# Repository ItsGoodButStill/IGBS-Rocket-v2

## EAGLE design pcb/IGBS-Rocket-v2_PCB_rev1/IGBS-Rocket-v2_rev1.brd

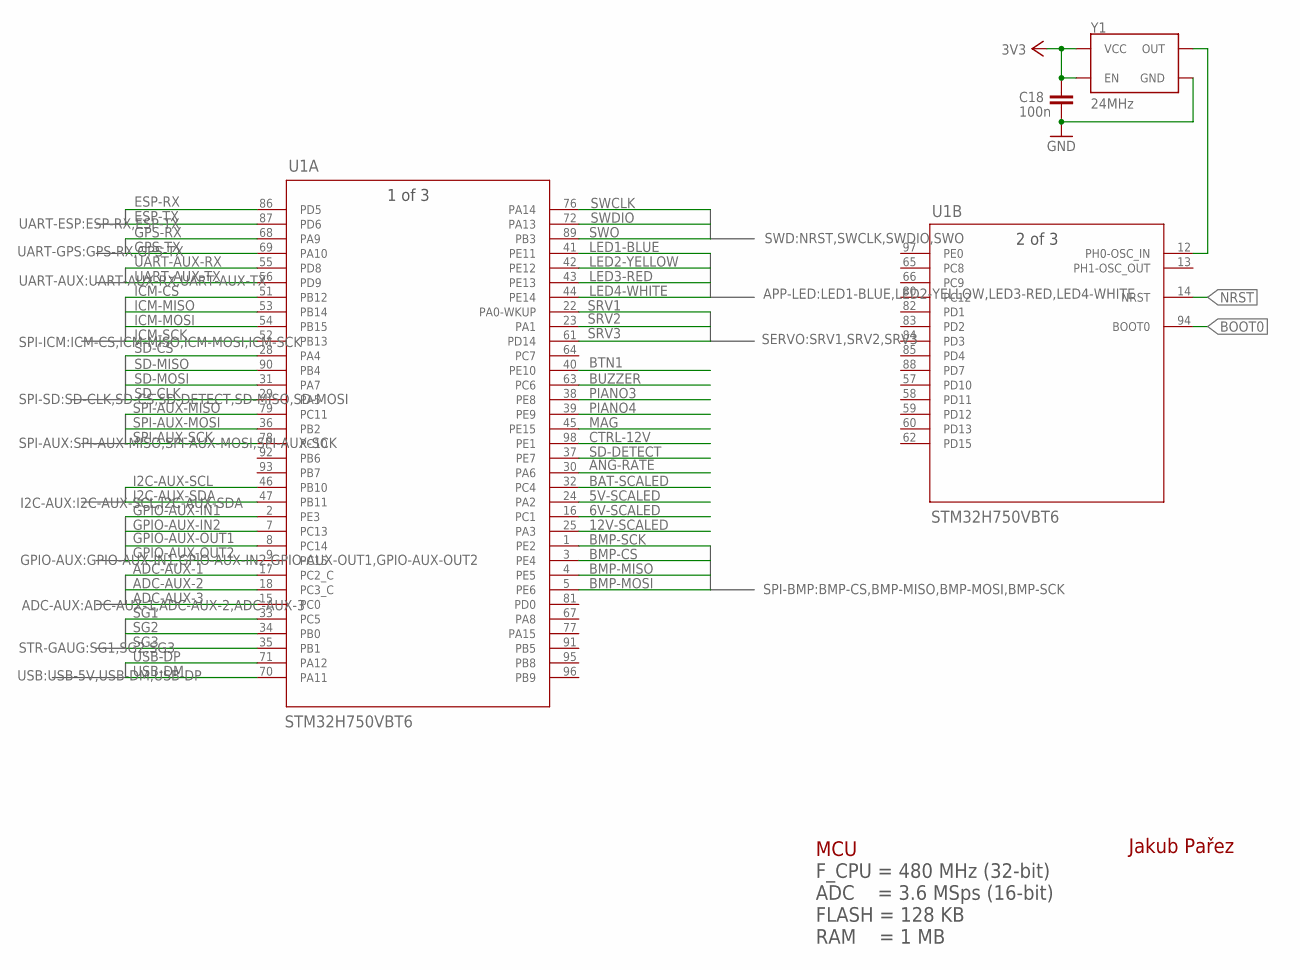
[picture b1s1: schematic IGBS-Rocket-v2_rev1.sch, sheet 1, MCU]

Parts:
C18: 100n; C0603K
U1: STM32H750VBT6; LQFP100-14X14MM
Y1: 24MHz; OSCILLATOR-SMD-7X5-4PAD

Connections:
3V3: C18.2, Y1.1 (EN), Y1.4 (VCC); also elsewhere on the board
5V-SCALED: U1.24 (PA2); also elsewhere on the board
6V-SCALED: U1.16 (PC1); also elsewhere on the board
12V-SCALED: U1.25 (PA3); also elsewhere on the board
ADC-AUX-1: U1.17 (PC2_C); also elsewhere on the board
ADC-AUX-2: U1.18 (PC3_C); also elsewhere on the board
ADC-AUX-3: U1.15 (PC0); also elsewhere on the board
ANG-RATE: U1.30 (PA6); also elsewhere on the board
BAT-SCALED: U1.32 (PC4); also elsewhere on the board
BMP-CS: U1.3 (PE4); also elsewhere on the board
BMP-MISO: U1.4 (PE5); also elsewhere on the board
BMP-MOSI: U1.5 (PE6); also elsewhere on the board
BMP-SCK: U1.1 (PE2); also elsewhere on the board
BOOT0: U1.94 (BOOT0); also elsewhere on the board
BTN1: U1.40 (PE10); also elsewhere on the board
BUZZER: U1.63 (PC6); also elsewhere on the board
CTRL-12V: U1.98 (PE1); also elsewhere on the board
ESP-RX: U1.86 (PD5); also elsewhere on the board
ESP-TX: U1.87 (PD6); also elsewhere on the board
GND: C18.1, Y1.2 (GND); also elsewhere on the board
GPIO-AUX-IN1: U1.2 (PE3); also elsewhere on the board
GPIO-AUX-IN2: U1.7 (PC13); also elsewhere on the board
GPIO-AUX-OUT1: U1.8 (PC14); also elsewhere on the board
GPIO-AUX-OUT2: U1.9 (PC15); also elsewhere on the board
GPS-RX: U1.68 (PA9); also elsewhere on the board
GPS-TX: U1.69 (PA10); also elsewhere on the board
I2C-AUX-SCL: U1.46 (PB10); also elsewhere on the board
I2C-AUX-SDA: U1.47 (PB11); also elsewhere on the board
ICM-CS: U1.51 (PB12); also elsewhere on the board
ICM-MISO: U1.53 (PB14); also elsewhere on the board
ICM-MOSI: U1.54 (PB15); also elsewhere on the board
ICM-SCK: U1.52 (PB13); also elsewhere on the board
LED1-BLUE: U1.41 (PE11); also elsewhere on the board
LED2-YELLOW: U1.42 (PE12); also elsewhere on the board
LED3-RED: U1.43 (PE13); also elsewhere on the board
LED4-WHITE: U1.44 (PE14); also elsewhere on the board
MAG: U1.45 (PE15); also elsewhere on the board
unnamed: U1.12 (PH0-OSC_IN), Y1.3 (OUT)
NRST: U1.14 (NRST); also elsewhere on the board
PIANO3: U1.38 (PE8); also elsewhere on the board
PIANO4: U1.39 (PE9); also elsewhere on the board
SD-CLK: U1.29 (PA5); also elsewhere on the board
SD-CS: U1.28 (PA4); also elsewhere on the board
SD-DETECT: U1.37 (PE7); also elsewhere on the board
SD-MISO: U1.90 (PB4); also elsewhere on the board
SD-MOSI: U1.31 (PA7); also elsewhere on the board
SG1: U1.33 (PC5); also elsewhere on the board
SG2: U1.34 (PB0); also elsewhere on the board
SG3: U1.35 (PB1); also elsewhere on the board
SPI-AUX-MISO: U1.79 (PC11); also elsewhere on the board
SPI-AUX-MOSI: U1.36 (PB2); also elsewhere on the board
SPI-AUX-SCK: U1.78 (PC10); also elsewhere on the board
SRV1: U1.22 (PA0-WKUP); also elsewhere on the board
SRV2: U1.23 (PA1); also elsewhere on the board
SRV3: U1.61 (PD14); also elsewhere on the board
SWCLK: U1.76 (PA14); also elsewhere on the board
SWDIO: U1.72 (PA13); also elsewhere on the board
SWO: U1.89 (PB3); also elsewhere on the board
UART-AUX-RX: U1.55 (PD8); also elsewhere on the board
UART-AUX-TX: U1.56 (PD9); also elsewhere on the board
USB-DM: U1.70 (PA11); also elsewhere on the board
USB-DP: U1.71 (PA12); also elsewhere on the board

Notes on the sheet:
MCU
Jakub Pařez
F_CPU = 480 MHz (32-bit) ADC = 3.6 MSps (16-bit) FLASH = 128 KB RAM = 1 MB

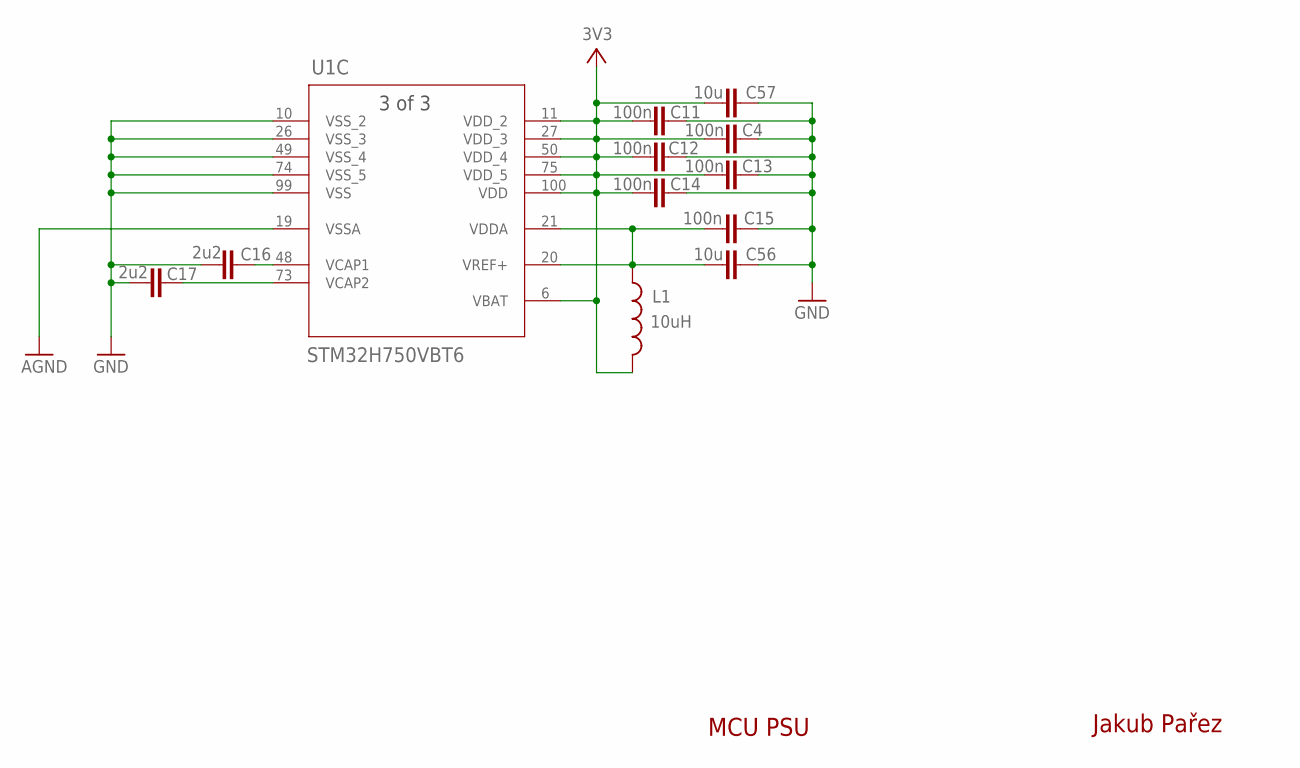
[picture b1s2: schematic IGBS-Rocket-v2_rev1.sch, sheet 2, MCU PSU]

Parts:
C4, C11, C12, C13, C14, C15: 100n; C0603K
C16, C17: 2u2; C0805K
C56, C57: 10u; 0805-CAP
L1: 10uH; 0805
U1: STM32H750VBT6; LQFP100-14X14MM

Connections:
3V3: C4.2, C11.2, C12.2, C13.2, C14.2, C57.1, L1.2, U1.6 (VBAT), U1.11 (VDD_2), U1.27 (VDD_3), U1.50 (VDD_4), U1.75 (VDD_5), U1.100 (VDD); also elsewhere on the board
AGND: U1.19 (VSSA)
GND: C4.1, C11.1, C12.1, C13.1, C14.1, C15.1, C16.2, C17.1, C56.2, C57.2, U1.10 (VSS_2), U1.26 (VSS_3), U1.49 (VSS_4), U1.74 (VSS_5), U1.99 (VSS); also elsewhere on the board
unnamed: C16.1, U1.48 (VCAP1)
unnamed: C17.2, U1.73 (VCAP2)
VDDA: C15.2, C56.1, L1.1, U1.20 (VREF+), U1.21 (VDDA)

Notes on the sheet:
MCU PSU
Jakub Pařez

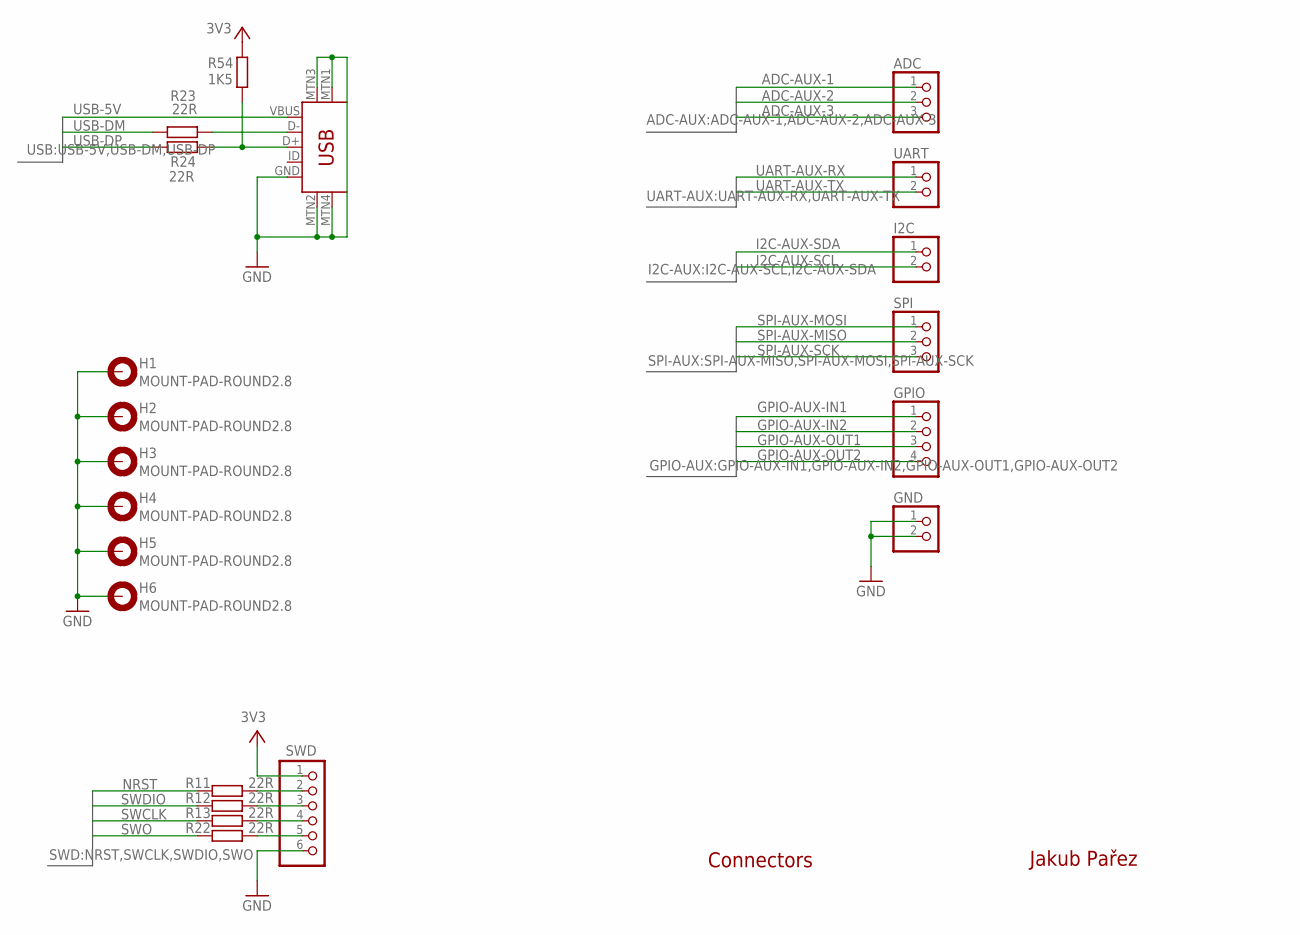
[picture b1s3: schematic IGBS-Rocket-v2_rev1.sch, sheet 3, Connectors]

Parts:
ADC: PINHD-1X3; 1X03
GND: PINHD-1X2; 1X02
GPIO: PINHD-1X4; 1X04
H1, H2, H3, H4, H5, H6: MOUNT-PAD-ROUND2.8; 2,8-PAD
I2C: PINHD-1X2; 1X02
R11, R12, R13, R22, R23, R24: 22R; R0603
R54: 1K5; R0603
SPI: PINHD-1X3; 1X03
SWD: PINHD-1X6; 1X06
UART: PINHD-1X2; 1X02
USB: USB-MINIB-5PIN; USB-MINIB

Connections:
3V3: R54.2, SWD.1; also elsewhere on the board
ADC-AUX-1: ADC.1; also elsewhere on the board
ADC-AUX-2: ADC.2; also elsewhere on the board
ADC-AUX-3: ADC.3; also elsewhere on the board
GND: GND.1, GND.2, H1.B2,8, H2.B2,8, H3.B2,8, H4.B2,8, H5.B2,8, H6.B2,8, SWD.6, USB.GND, USB.MTN1 (MTN2), USB.MTN2 (MTN3), USB.MTN3 (MTN1), USB.MTN4; also elsewhere on the board
GPIO-AUX-IN1: GPIO.1; also elsewhere on the board
GPIO-AUX-IN2: GPIO.2; also elsewhere on the board
GPIO-AUX-OUT1: GPIO.3; also elsewhere on the board
GPIO-AUX-OUT2: GPIO.4; also elsewhere on the board
I2C-AUX-SCL: I2C.2; also elsewhere on the board
I2C-AUX-SDA: I2C.1; also elsewhere on the board
unnamed: R11.1, SWD.2
unnamed: R12.1, SWD.3
unnamed: R13.1, SWD.4
unnamed: R22.1, SWD.5
unnamed: R23.1, USB.D-
unnamed: R24.1, R54.1, USB.D+
NRST: R11.2; also elsewhere on the board
SPI-AUX-MISO: SPI.2; also elsewhere on the board
SPI-AUX-MOSI: SPI.1; also elsewhere on the board
SPI-AUX-SCK: SPI.3; also elsewhere on the board
SWCLK: R13.2; also elsewhere on the board
SWDIO: R12.2; also elsewhere on the board
SWO: R22.2; also elsewhere on the board
UART-AUX-RX: UART.1; also elsewhere on the board
UART-AUX-TX: UART.2; also elsewhere on the board
USB-5V: USB.VBUS
USB-DM: R23.2; also elsewhere on the board
USB-DP: R24.2; also elsewhere on the board

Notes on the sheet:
Connectors
Jakub Pařez

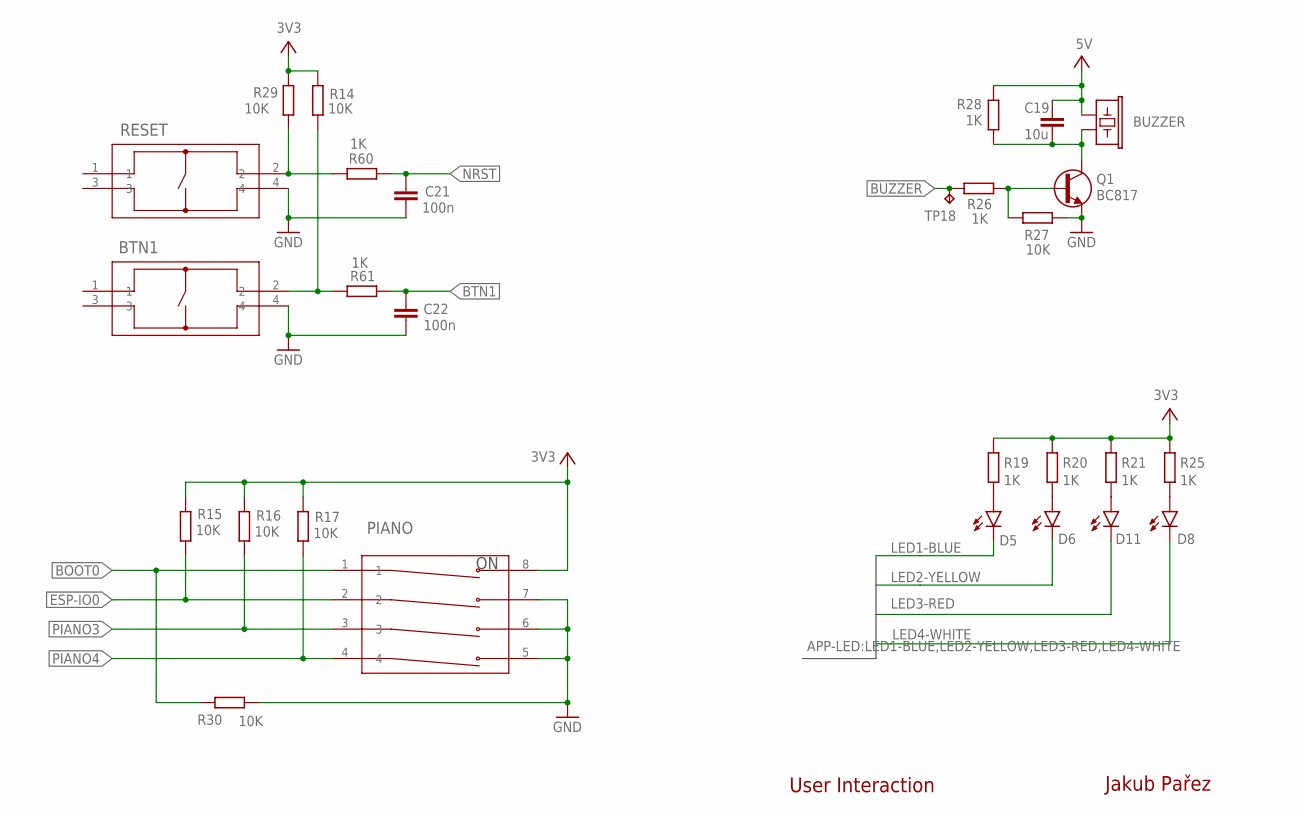
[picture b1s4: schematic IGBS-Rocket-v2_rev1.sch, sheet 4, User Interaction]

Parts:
BTN1: B3FS-1000SW_B3FS-1000_OMR; SW_B3FS-1000_OMR
BUZZER: BUZZERPTH; BUZZER-12MM
C19: 10u; 0805-CAP
C21, C22: 100n; C0603K
D5, D6, D8, D11: GREEN; LED-1206
PIANO: A6FR-4101SW_A6FR-4101_OMR; SW_A6FR-4101_OMR
Q1: BC817; SOT23-BEC
R14, R15, R16, R17, R27, R29, R30: 10K; R0603
R19, R20, R21, R25, R26, R28, R60, R61: 1K; R0603
RESET: B3FS-1000SW_B3FS-1000_OMR; SW_B3FS-1000_OMR
TP18: TPB1,27; B1,27

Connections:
3V3: PIANO.8, R14.1, R15.2, R16.2, R17.2, R19.2, R20.2, R21.2, R25.2, R29.1; also elsewhere on the board
5V: BUZZER.+ (1), C19.1, R28.1; also elsewhere on the board
5V-BUZZER: BUZZER.- (2), C19.2, Q1.C, R28.2
BOOT0: PIANO.1, R30.1; also elsewhere on the board
BTN1: C22.1, R61.2; also elsewhere on the board
BTN12: BTN1.2, R14.2, R61.1
BUZZER: R26.2, TP18.TP; also elsewhere on the board
ESP-IO0: PIANO.2, R15.1; also elsewhere on the board
GND: BTN1.4, C21.2, C22.2, PIANO.5, PIANO.6, PIANO.7, Q1.E, R27.1, R30.2, RESET.4; also elsewhere on the board
LED1-BLUE: D5.C; also elsewhere on the board
LED2-YELLOW: D6.C; also elsewhere on the board
LED3-RED: D11.C; also elsewhere on the board
LED4-WHITE: D8.C; also elsewhere on the board
unnamed: D8.A, R25.1
unnamed: D5.A, R19.1
unnamed: D6.A, R20.1
unnamed: D11.A, R21.1
unnamed: Q1.B, R26.1, R27.2
NRST: C21.1, R60.2; also elsewhere on the board
NRST2: R29.2, R60.1, RESET.2
PIANO3: PIANO.3, R16.1; also elsewhere on the board
PIANO4: PIANO.4, R17.1; also elsewhere on the board

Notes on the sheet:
User Interaction
Jakub Pařez

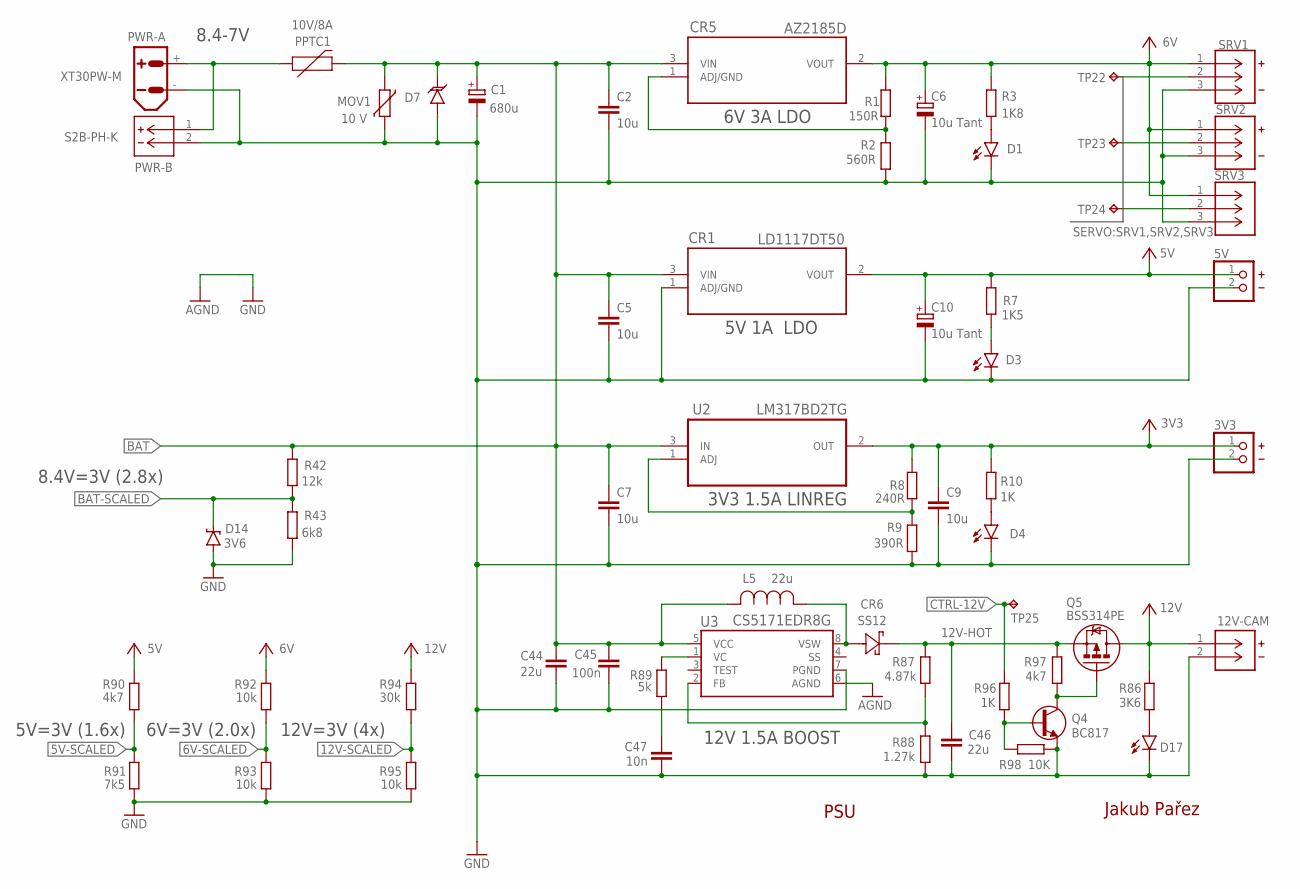
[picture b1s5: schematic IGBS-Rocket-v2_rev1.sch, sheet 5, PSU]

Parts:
3V3, 5V: PINHD-1X2; 1X02
12V-CAM: S2B-XH-A(LF)(SN)CONN_S2B-XH-A_JST; CONN_S2B-XH-A_JST
C1: 680u; TT2D7L
C2, C5, C7, C9: 10u; 0805-CAP
C6, C10: 10u Tant; CT3216
C44, C46: 22u; 0805-CAP
C45: 100n; C0805K
C47: 10n; C0805K
CR1: LD1117DT50; DPAK229P990X239-3N
CR5: AZ2185D; DPAK229P990X239-3N
CR6: SS12; DIODE_DO214AC
D1, D3, D4, D17: GREEN; LED-1206
D7: TVSSMA; SMA-DIODE
D14: 3V6; SOD-123
L5: 22u; IND_74437_WRE
MOV1: 10 V; CT/CN0805
PPTC1: 10V/8A; 1210
PWR-A: XT30PW-M
PWR-B: S2B-PH-K-S; CONN_S2B-PH-K-S_JST
Q4: BC817; SOT23-BEC
Q5: BSS314PE; SOT23-3
R1: 150R; R0603
R2: 560R; R0603
R3: 1K8; R0603
R7: 1K5; R0603
R8: 240R; R0603
R9: 390R; R0603
R10, R96: 1K; R0603
R42: 12k; R0603
R43: 6k8; R0603
R86: 3K6; R0603
R87: 4.87k; R0603
R88: 1.27k; R0603
R89: 5k; R0603
R90, R97: 4k7; R0603
R91: 7k5; R0603
R92, R93, R95: 10k; R0603
R94: 30k; R0603
R98: 10K; R0603
SRV1: S3B-XH-A; CONN_S3B-XH-A(LF)(SN)_JST
SRV2, SRV3: S3B-XH-A(LF)(SN)CONN_S3B-XH-A(LF)(SN)_JST; CONN_S3B-XH-A(LF)(SN)_JST
TP22, TP23, TP24, TP25: TPB1,27; B1,27
U2: LM317BD2TG; TO263
U3: CS5171EDR8G; SOIC8_ONS

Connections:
3V3: 3V3.1, C9.1, R8.2, R10.2, U2.2 (OUT); also elsewhere on the board
5V: 5V.1, C10.+, CR1.2 (VOUT), R7.2, R90.2; also elsewhere on the board
5V-SCALED: R90.1, R91.2; also elsewhere on the board
6V: C6.+, CR5.2 (VOUT), R1.2, R3.2, R92.2, SRV1.1, SRV2.1, SRV3.1
6V-SCALED: R92.1, R93.2; also elsewhere on the board
12V: 12V-CAM.1, Q5.3 (D), R86.2, R94.2
12V-FB: CR6.2, L5.1, U3.8 (VSW)
12V-HOT: C46.1, CR6.1, Q5.2 (S), R87.2, R97.1
12V-SCALED: R94.1, R95.2; also elsewhere on the board
BAT: C1.+, C2.1, C5.1, C7.1, C44.1, C45.2, CR1.3 (VIN), CR5.3 (VIN), D7.C, L5.2, MOV1.1, PPTC1.2, R42.2, U2.3 (IN), U3.5 (VCC); also elsewhere on the board
BAT2: PPTC1.1, PWR-A.+, PWR-B.1
BAT-SCALED: D14.C, R42.1, R43.2; also elsewhere on the board
CTRL-12V: R96.2, TP25.TP; also elsewhere on the board
GND: 3V3.2, 5V.2, 12V-CAM.2, C1.-, C2.2, C5.2, C6.-, C7.2, C9.2, C10.-, C44.2, C45.1, C46.2, C47.1, CR1.1 (ADJ/GND), D1.C, D3.C, D4.C, D7.A, D14.A, D17.C, MOV1.2, PWR-A.-, PWR-B.2, Q4.E, R2.1, R9.1, R43.1, R88.1, R91.1, R93.1, R95.1, R98.1, SRV1.3, SRV2.3, SRV3.3, U3.6 (AGND), U3.7 (PGND); also elsewhere on the board
unnamed: CR5.1 (ADJ/GND), R1.1, R2.2
unnamed: D1.A, R3.1
unnamed: D3.A, R7.1
unnamed: R8.1, R9.2, U2.1 (ADJ)
unnamed: D4.A, R10.1
unnamed: R87.1, R88.2, U3.2 (FB)
unnamed: D17.A, R86.1
unnamed: Q4.B, R96.1, R98.2
unnamed: C47.2, R89.1
unnamed: R89.2, U3.1 (VC)
unnamed: Q4.C, Q5.1 (G), R97.2
SRV1: SRV1.2, TP22.TP; also elsewhere on the board
SRV2: SRV2.2, TP23.TP; also elsewhere on the board
SRV3: SRV3.2, TP24.TP; also elsewhere on the board

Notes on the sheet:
PSU
Jakub Pařez
3V3 1.5A LINREG
6V 3A LDO
5V 1A LDO
8.4-7V
S2B-PH-K
8.4V=3V (2.8x)
12V 1.5A BOOST
5V=3V (1.6x)
6V=3V (2.0x)
12V=3V (4x)

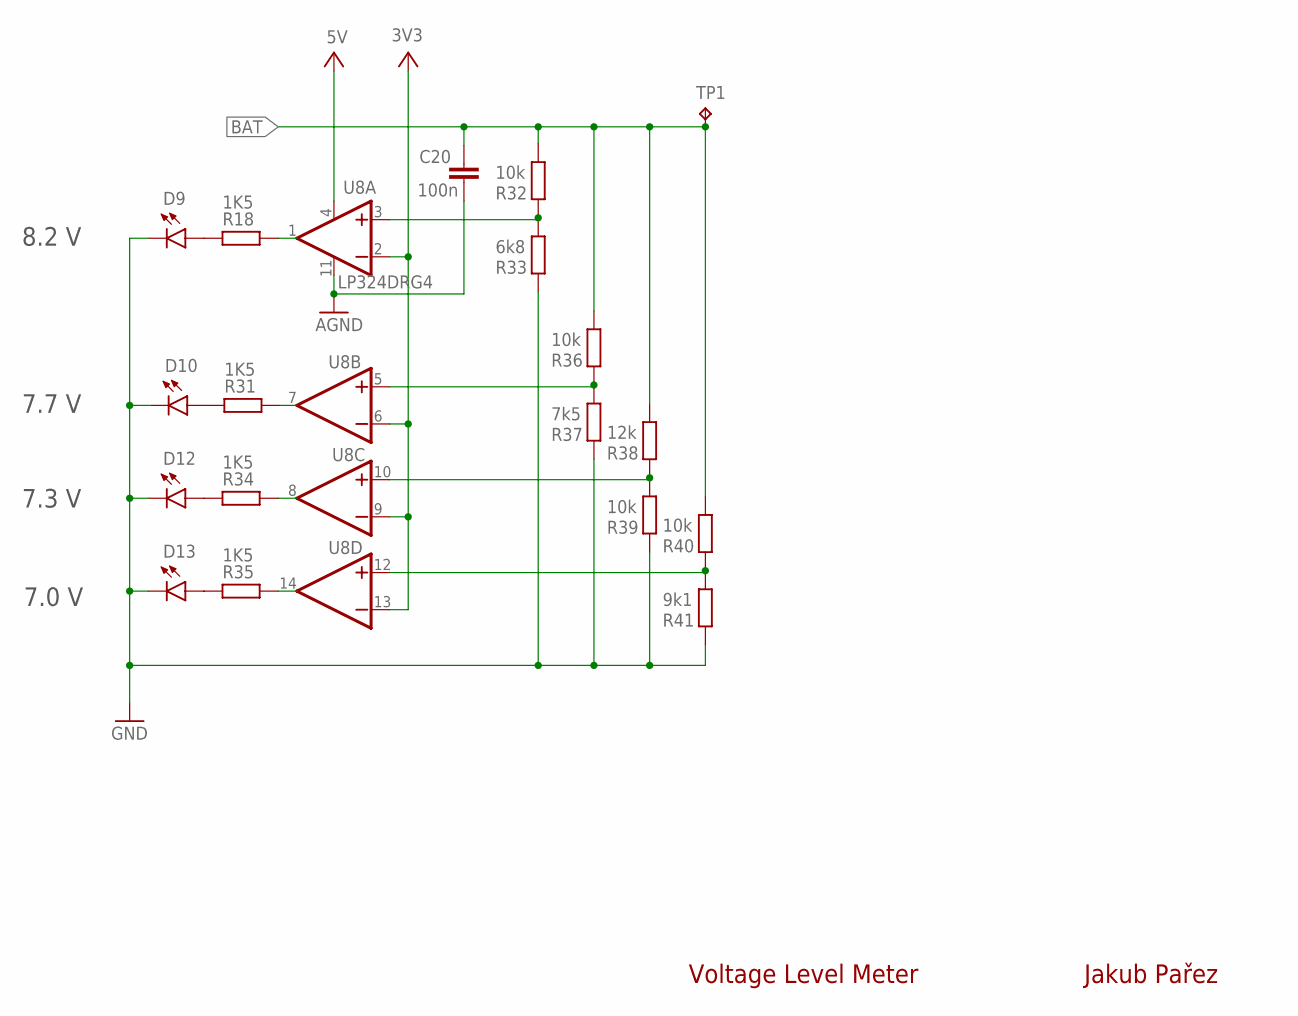
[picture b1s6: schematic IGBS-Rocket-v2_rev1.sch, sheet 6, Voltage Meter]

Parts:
C20: 100n; C0603K
D9, D10, D12, D13: GREEN; LED-1206
R18, R31, R34, R35: 1K5; R0603
R32, R36, R39, R40: 10k; R0603
R33: 6k8; R0603
R37: 7k5; R0603
R38: 12k; R0603
R41: 9k1; R0603
TP1: TPB2,54; B2,54
U8: LP324DRG4; D14

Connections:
3V3: U8.2 (-), U8.6 (-), U8.9 (-), U8.13 (-); also elsewhere on the board
5V: U8.4 (VCC); also elsewhere on the board
BAT: C20.2, R32.2, R36.2, R38.2, R40.2, TP1.TP; also elsewhere on the board
GND: C20.1, D9.C, D10.C, D12.C, D13.C, R33.1, R37.1, R39.1, R41.1, U8.11 (GND); also elsewhere on the board
unnamed: D9.A, R18.1
unnamed: D10.A, R31.1
unnamed: D12.A, R34.1
unnamed: D13.A, R35.1
unnamed: R35.2, U8.14 (OUT)
unnamed: R34.2, U8.8 (OUT)
unnamed: R31.2, U8.7 (OUT)
unnamed: R18.2, U8.1 (OUT)
unnamed: R32.1, R33.2, U8.3 (+)
unnamed: R36.1, R37.2, U8.5 (+)
unnamed: R38.1, R39.2, U8.10 (+)
unnamed: R40.1, R41.2, U8.12 (+)

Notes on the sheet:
Voltage Level Meter
8.2 V
7.7 V
7.3 V
7.0 V
Jakub Pařez

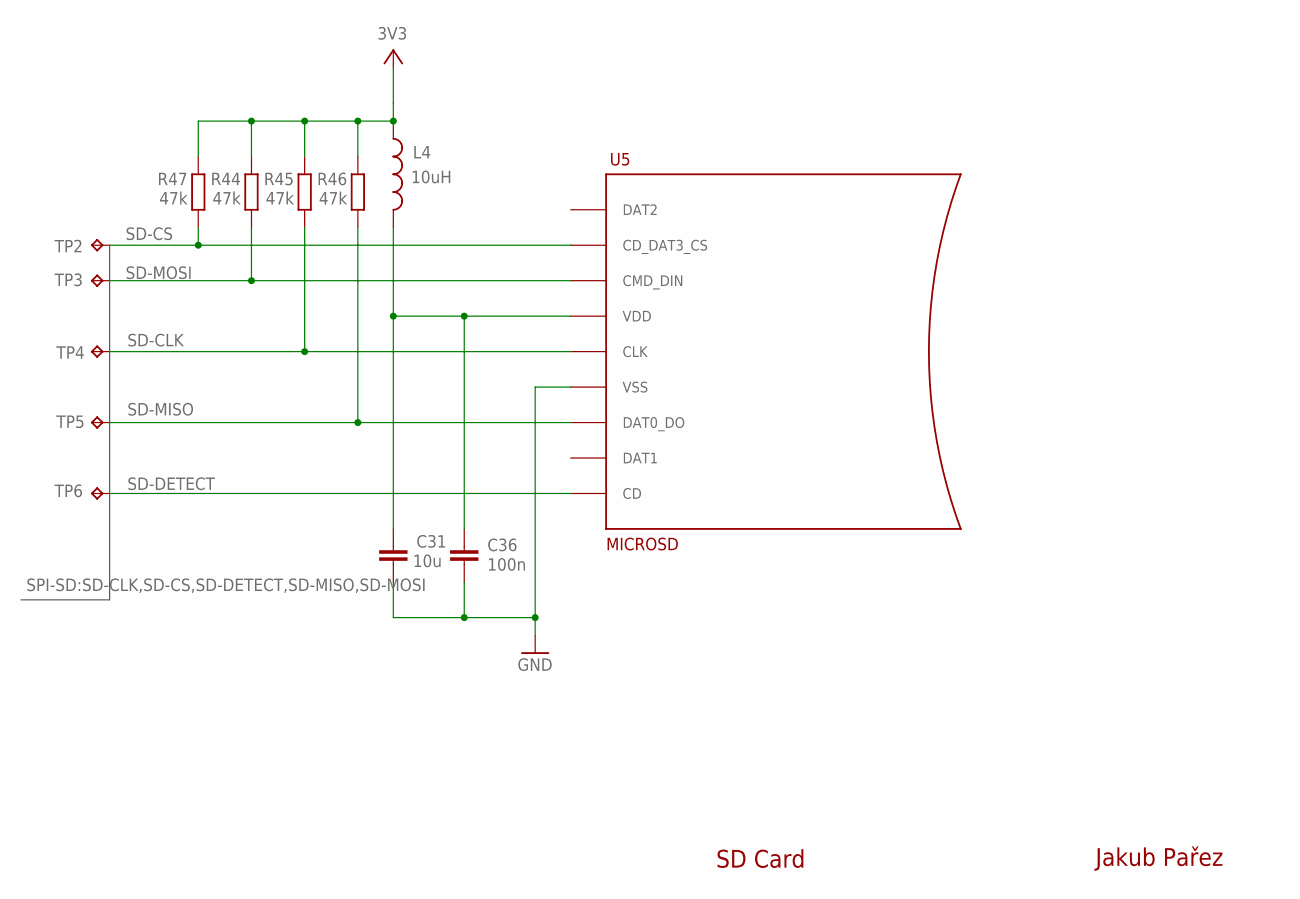
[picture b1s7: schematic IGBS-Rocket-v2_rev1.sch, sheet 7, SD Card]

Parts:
C31: 10u; 0805-CAP
C36: 100n; C0603K
L4: 10uH; 0805
R44, R45, R46, R47: 47k; R0603
TP2, TP3, TP4, TP5, TP6: TPB1,27; B1,27
U5: MICROSD; MICROSD-PUSH-OUT

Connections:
3V3: L4.1, R44.2, R45.2, R46.2, R47.2; also elsewhere on the board
3V3-SD: C31.1, C36.1, L4.2, U5.4 (VDD)
GND: C31.2, C36.2, U5.6 (VSS), U5.G1 (VSS), U5.G2 (VSS), U5.G3 (VSS), U5.G4 (VSS); also elsewhere on the board
SD-CLK: R45.1, TP4.TP, U5.5 (CLK); also elsewhere on the board
SD-CS: R47.1, TP2.TP, U5.2 (CD_DAT3_CS); also elsewhere on the board
SD-DETECT: TP6.TP, U5.CD; also elsewhere on the board
SD-MISO: R46.1, TP5.TP, U5.7 (DAT0_DO); also elsewhere on the board
SD-MOSI: R44.1, TP3.TP, U5.3 (CMD_DIN); also elsewhere on the board

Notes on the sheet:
SD Card
Jakub Pařez

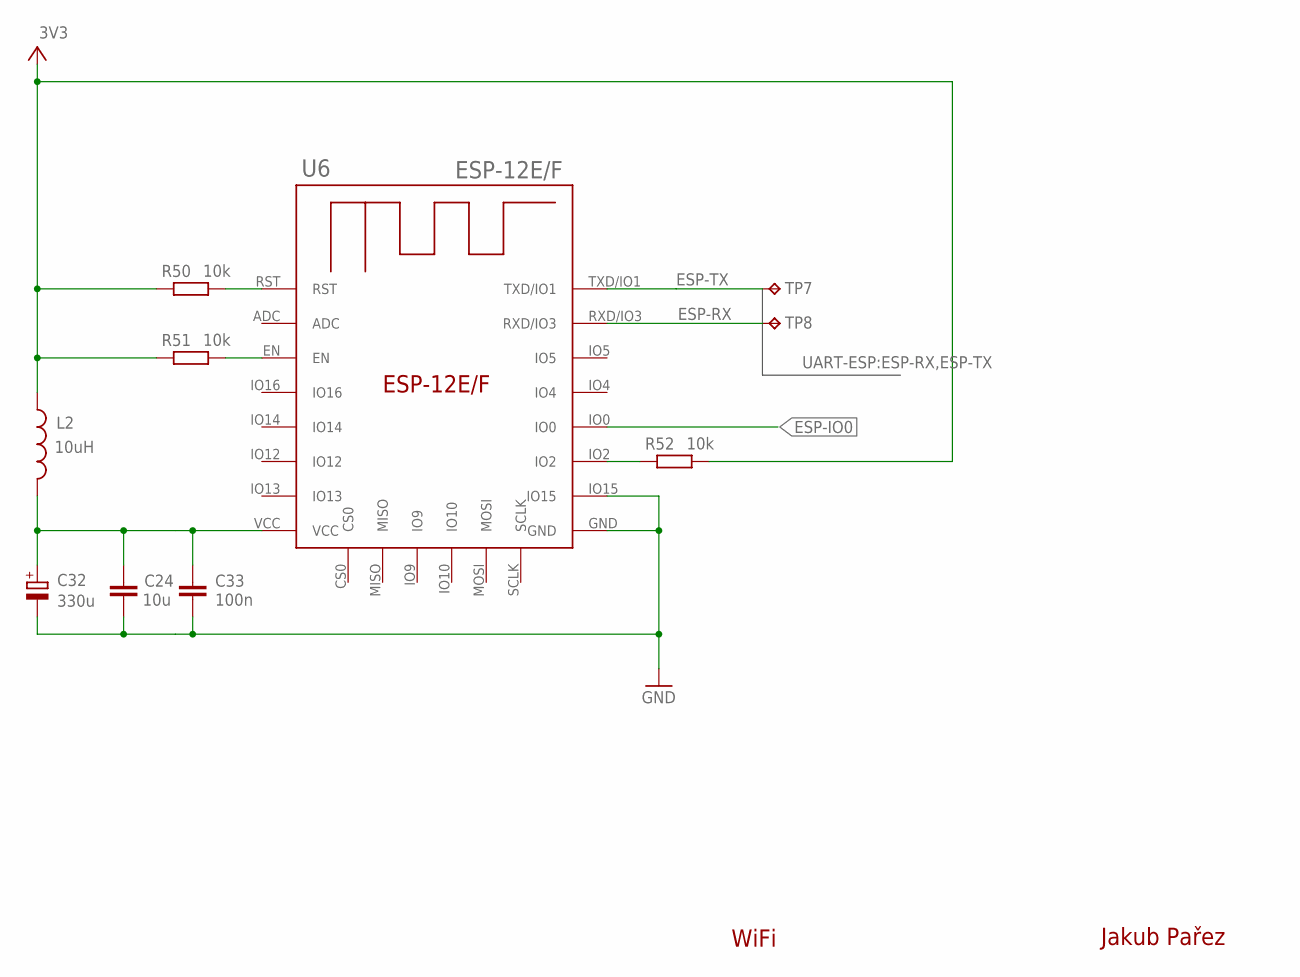
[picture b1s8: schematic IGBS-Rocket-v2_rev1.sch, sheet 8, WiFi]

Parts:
C24: 10u; 0805-CAP
C32: 330u; E2,5-7
C33: 100n; C0603K
L2: 10uH; 0805
R50, R51, R52: 10k; R0603
TP7, TP8: TPB1,27; B1,27
U6: ESP-12E/F; ESP-12E

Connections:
3V3: L2.1, R50.2, R51.2, R52.1; also elsewhere on the board
3V3-ESP: C24.1, C32.+, C33.1, L2.2, U6.VCC
ESP-IO0: U6.IO0; also elsewhere on the board
ESP-RX: TP8.TP, U6.RXD/IO3; also elsewhere on the board
ESP-TX: TP7.TP, U6.TXD/IO1; also elsewhere on the board
GND: C24.2, C32.-, C33.2, U6.GND, U6.IO15; also elsewhere on the board
unnamed: R50.1, U6.RST
unnamed: R51.1, U6.EN
unnamed: R52.2, U6.IO2

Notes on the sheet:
WiFi
Jakub Pařez

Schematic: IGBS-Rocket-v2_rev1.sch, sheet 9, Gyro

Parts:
C25, C29: 100n; C0603K
C26, C27: 4u7; C0805K
C28: 1u8; C0805K
D2, D15: 3V6; SOD-123
Q2: ENC-03; ENC-03RC
R48: 100k; R0603
R49: 10k; R0603
R53: 59k; R0603
R57: 1k; R0603
TP9: TPB1,27; B1,27
U9: MCP6V51T-E/MS; MSOP8_MS_MCH

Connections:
3V3: D2.C; also elsewhere on the board
5V: C25.2, C29.2, Q2.3 (VCC), U9.7 (VCC); also elsewhere on the board
ANG-RATE: D2.A, D15.C, R57.1, TP9.TP; also elsewhere on the board
ANG-RATE2: C28.2, R53.1, R57.2, U9.6 (OUT)
GND: C25.1, C27.2, C29.1, D15.A, Q2.2 (GND), U9.4 (GND); also elsewhere on the board
unnamed: C26.2, Q2.4 (OUT)
unnamed: C26.1, R48.2, U9.3 (+)
unnamed: C27.1, Q2.1 (VREF), R48.1, R49.1
unnamed: C28.1, R49.2, R53.2, U9.2 (-)

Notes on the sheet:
Gyro
Jakub Pařez
GAIN = 6.9 OUTPUT = 1.35 +- (0.2 * 6.9) V RANGE = 0 - 2.73 V

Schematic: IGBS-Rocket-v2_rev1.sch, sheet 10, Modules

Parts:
BT1: MS621FE-3V; BATTCON-6.8MM
C23, C48, C49, C50, C51, C52, C53, C54: 100n; C0603K
C55: 10u; 0805-CAP
D16, D19: 1N4148; SOD-123
D18: GREEN; LED-1206
J1: U.FL
L3: 10uH; 0805
L6: 27nH; C0402
MAG: S2B-XH-A(LF)(SN)CONN_S2B-XH-A_JST; CONN_S2B-XH-A_JST
Q3: BSS316N; SOT23-3
R55: 10R; R0603
R56, R99: 1k; R0603
R58: 22R; R0603
R59: 100k; R0603
TP10, TP11, TP12, TP13, TP14, TP15, TP16, TP17, TP19, TP20, TP21: TPB1,27; B1,27
U4: MPU-9250; QFN40P300X300X105-24N
U7: BMP280; XDCR_BMP280
U10: 24AA32A-I/ST; TSSOP8_MC_MCH
U11: u-blox NEO-M6; NEO-M8

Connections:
3V3: C48.2, C49.2, C50.2, C52.2, C54.1, L3.2, U4.8 (VDDIO), U4.13 (VDD), U7.6 (VDDIO), U7.8 (VDD), U10.8 (VCC); also elsewhere on the board
5V: C23.1, D16.C, MAG.1; also elsewhere on the board
5V-MAG: D16.A, MAG.2, Q3.3 (D)
BMP-CS: TP17.TP, U7.2 (CSB); also elsewhere on the board
BMP-MISO: TP10.TP, U7.5 (SDO); also elsewhere on the board
BMP-MOSI: TP16.TP, U7.3 (SDI); also elsewhere on the board
BMP-SCK: TP11.TP, U7.4 (SCK); also elsewhere on the board
GND: BT1.-, C23.2, C48.1, C49.1, C50.1, C51.1, C52.1, C53.2, C54.2, C55.2, D18.C, J1.P$1 (GND), J1.P$2 (GND), Q3.2 (S), R59.1, U4.1 (RESV_1), U4.18 (GND), U4.19 (RESV_19), U4.20 (RESV_20), U7.1 (GND), U7.7 (GND), U10.1 (A0), U10.2 (A1), U10.3 (A2), U10.4 (VSS), U10.7 (WP), U11.10 (10_GND), U11.12 (12_GND), U11.13 (13_GND), U11.24 (24_GND); also elsewhere on the board
GPS-RF-IN: J1.P$3 (SIGNAL), L6.1, U11.11 (11_RF_IN)
GPS-RX: TP19.TP, U11.21 (21_RXD/SPI_MOSI); also elsewhere on the board
GPS-TX: TP20.TP, U11.20 (20_TXD/SPI_MISO); also elsewhere on the board
GPS-VBCKP: BT1.+, R99.2, U11.22 (22_V_BCKP)
GPS-VBCKP2: D19.C, R99.1
GPS-VCC: C53.1, C55.1, D19.A, L3.1, U11.23 (23_VCC)
GPS-VCC-RF: R55.2, U11.8 (8_RESET_N), U11.9 (9_VCC_RF)
ICM-CS: TP14.TP, U4.22 (!CS); also elsewhere on the board
ICM-MISO: TP15.TP, U4.9 (AD0/SDO); also elsewhere on the board
ICM-MOSI: TP13.TP, U4.24 (SDA/SDI); also elsewhere on the board
ICM-SCK: TP12.TP, U4.23 (SCL/SCLK); also elsewhere on the board
MAG: R58.1, TP21.TP; also elsewhere on the board
unnamed: Q3.1 (G), R58.2, R59.2
unnamed: U10.6 (SCL), U11.19 (19_SCL/SPI_CLK)
unnamed: U10.5 (SDA), U11.18 (18_SDA/SPI_CS_N)
unnamed: C51.2, U4.10 (REGOUT)
unnamed: D18.A, R56.1
unnamed: L6.2, R55.1
unnamed: R56.2, U11.3 (3_TIMEPULSE)

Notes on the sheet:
IMU, GPS, MAGNET, BARO
Jakub Pařez

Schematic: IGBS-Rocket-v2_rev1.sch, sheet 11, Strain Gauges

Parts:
C3, C35, C40: 100n; C0603K
C8, C30, C34, C37, C38, C39, C41, C42, C43: 1u; C0603K
CR2, CR3, CR4: TS4040DILT-2.5; SOT23_TO-236AB_NEX
IC1, IC2, IC3: NCV21872DR2G; SO08
R4, R68, R77: 500k; RES_C01R00
R5, R69, R78: 10k; R0603
R6, R62, R63, R70, R71, R72, R79, R80, R81: 360R; R0603
R64, R66, R73, R75, R82, R84: 470k; R0603
R65, R74, R83: 20k; R0603
R67, R76, R85: 330R; R0603
SG1, SG2, SG3: S3B-XH-A; CONN_S2B-XH-A_JST
TP26, TP27, TP28: TPB1,27; B1,27

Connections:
5V: C3.2, C35.2, C40.2, IC1.8 (V+), IC2.8 (V+), IC3.8 (V+), R67.2, R76.2, R85.2; also elsewhere on the board
GND: C3.1, C8.1, C30.1, C34.1, C35.1, C37.1, C38.1, C39.1, C40.1, C41.1, C42.1, C43.1, CR2.2, CR2.3, CR3.2, CR3.3, CR4.2, CR4.3, IC1.4 (V-), IC2.4 (V-), IC3.4 (V-), R4.3, R6.2, R62.2, R68.3, R70.2, R71.2, R77.3, R79.2, R80.2; also elsewhere on the board
unnamed: R69.2, R70.1, SG2.1
unnamed: R5.2, R6.1, SG1.1
unnamed: C8.2, IC1.3 (+IN), R62.1, R63.2
unnamed: C37.2, IC2.3 (+IN), R71.1, R72.2
unnamed: IC1.2 (-IN), R5.1, R64.2
unnamed: IC1.1 (OUT), R64.1, R65.2
unnamed: IC1.6 (-IN), R65.1, R66.2
unnamed: C34.2, IC1.5 (+IN), R4.2
unnamed: CR2.1, R4.1, R63.1, R67.1, SG1.2
unnamed: IC2.2 (-IN), R69.1, R73.2
unnamed: IC2.1 (OUT), R73.1, R74.2
unnamed: IC2.6 (-IN), R74.1, R75.2
unnamed: C39.2, IC2.5 (+IN), R68.2
unnamed: CR3.1, R68.1, R72.1, R76.1, SG2.2
unnamed: R78.2, R79.1, SG3.1
unnamed: C41.2, IC3.3 (+IN), R80.1, R81.2
unnamed: IC3.2 (-IN), R78.1, R82.2
unnamed: IC3.1 (OUT), R82.1, R83.2
unnamed: IC3.6 (-IN), R83.1, R84.2
unnamed: C43.2, IC3.5 (+IN), R77.2
unnamed: CR4.1, R77.1, R81.1, R85.1, SG3.2
SG1: C30.2, IC1.7 (OUT), R66.1, TP26.TP; also elsewhere on the board
SG2: C38.2, IC2.7 (OUT), R75.1, TP27.TP; also elsewhere on the board
SG3: C42.2, IC3.7 (OUT), R84.1, TP28.TP; also elsewhere on the board

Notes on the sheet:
Strain Gauges
Jakub Pařez
STRAIN = 360 Ω GAIN = 48 + (0 - 24.5) VOLT = 0 - 3.6V

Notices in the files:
parts and their libraries:
SparkFun-Electromechanical: Licensing: Creative Commons ShareAlike 4.0 International - https://creativecommons.org/licenses/by-sa/4.0
COPYRIGHT: Copyright (C) 2022 Ultra Librarian. All rights reserved.
